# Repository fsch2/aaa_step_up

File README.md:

# aaa_step_up

This is a small step-up converter board small enough to replace an AAA battery. It is based on the MAX1896 DC-DC converter, which can provide up to 550 mA.

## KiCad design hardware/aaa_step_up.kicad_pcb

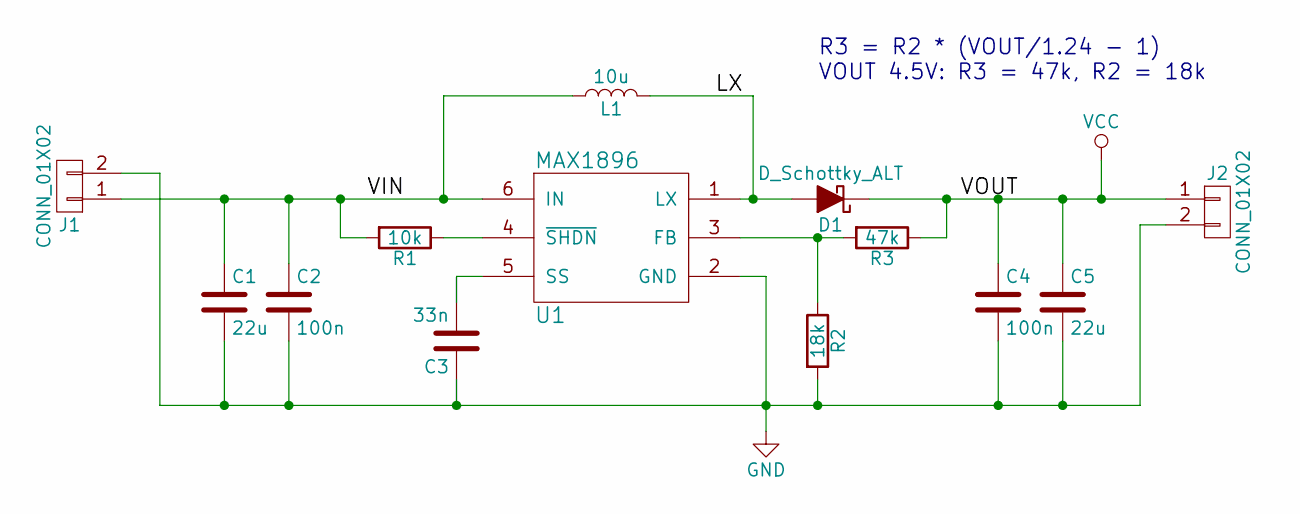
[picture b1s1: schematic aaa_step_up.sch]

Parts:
C1, C5: 22u; C_1206
C2, C4: 100n; C_0603
C3: 33n; C_0603
D1: D_Schottky_ALT; D_0805
J1, J2: CONN_01X02; Pin_Header_Straight_1x02_Pitch2.54mm
L1: 10u; Inductor_Taiyo-Yuden_NR-40xx
R1: 10k; R_0603
R2: 18k; R_0603
R3: 47k; R_0603
U1: MAX1896; SOT-23-6

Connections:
/LX: D1.2 (A), L1.2, U1.1 (LX)
/VIN: C1.1, C2.1, J1.1, L1.1, R1.2, U1.6 (IN)
GND: C1.2, C2.2, C3.1, C4.2, C5.2, J1.2, J2.2, R2.2, U1.2 (GND)
unnamed: C3.2, U1.5 (SS)
unnamed: R1.1, U1.4 (~SHDN)
unnamed: R2.1, R3.2, U1.3 (FB)
VCC: C4.1, C5.1, D1.1 (K), J2.1, R3.1

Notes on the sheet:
R3 = R2 * (VOUT/1.24 - 1) VOUT 4.5V: R3 = 47k, R2 = 18k

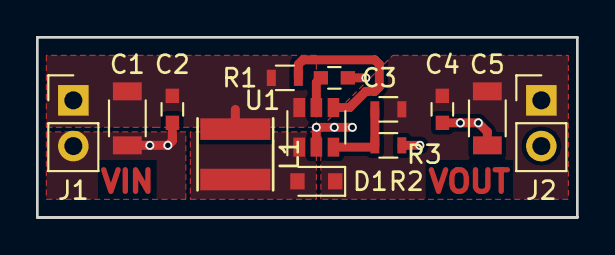
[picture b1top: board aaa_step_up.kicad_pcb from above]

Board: 2 copper layers, 30.0 x 10.0 mm, 13 parts (0 on the bottom side), 7 nets.

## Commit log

2017-09-16 Add kicad project
2017-09-16 Add pics of finished board.
2017-09-16 Add PCB clip to fix board in an AAA battery holder
2017-09-19 Add PDF of schematic sheet
2017-09-26 Add new version of clip with conical base
